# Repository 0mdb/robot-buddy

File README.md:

# Robot Buddy

A kid-safe, expressive robot platform combining real-time motor control, an animated TFT face, and optional networked AI planner.

## How It Works

Two ESP32-S3 microcontrollers handle the deterministic, safety-critical work: one drives motors with PID control and enforces safety limits, the other renders an animated face on a 320x240 TFT touch display (`esp32-face`). A Raspberry Pi 5 orchestrates everything at 50 Hz — reading sensors, running the state machine, applying layered safety policies, and streaming telemetry to a browser UI. An optional AI planner server on a separate machine (3090 Ti) generates expressive behavior plans via a local LLM.

Reflexes are local and deterministic. Planner is remote and optional.

## Hardware

| Component | Hardware | Role |
|---|---|---|
| Supervisor | Raspberry Pi 5 | 50 Hz orchestration, safety policy, HTTP/WS API |
| Face MCU | ESP32-S3 (Freenove FNK0104) | 320x240 TFT face renderer + touch/buttons telemetry |
| Reflex MCU | ESP32-S3 WROOM | Differential drive, PID, encoders, IMU, ultrasonic, safety |
| AI Server | PC with 3090 Ti (off-robot) | Planner/conversation LLM + TTS on LAN (`LLM_BACKEND=ollama|vllm`) |
| Motor Driver | TB6612FNG | Dual H-bridge for differential drive |
| Power | 2S LiPo | Split into dirty (motors) and clean 5V regulated rails |

## Repository Layout

```
robot-buddy/
├── supervisor/       # Python supervisor (Raspberry Pi 5, process-isolated workers)
│   ├── core/            # 50 Hz tick loop, state machine, safety, behavior engine
│   ├── devices/         # MCU clients (reflex, face), protocol, expressions
│   ├── io/              # Serial transport, COBS framing, CRC
│   ├── workers/         # Process-isolated workers (TTS, vision, AI)
│   ├── messages/        # NDJSON envelope, event/action types
│   ├── api/             # FastAPI HTTP/WebSocket server, param registry
│   ├── mock/            # Mock Reflex MCU for testing (PTY-based)
│   ├── tests/           # pytest test suite
│   └── pyproject.toml   # Package metadata, deps
├── server/              # AI planner server (3090 Ti, FastAPI + backend switch)
│   ├── app/             # FastAPI app, LLM/STT/TTS backends, prompts, schemas
│   ├── tests/           # pytest test suite
│   ├── Modelfile        # Legacy Ollama model config
│   └── pyproject.toml   # Package metadata, deps
├── esp32-face/       # Face MCU firmware (ESP32-S3, C/C++, ESP-IDF)
│   └── main/            # TFT face rendering + touch/buttons + USB protocol
├── esp32-reflex/        # Reflex MCU firmware (ESP32-S3, C/C++, ESP-IDF)
│   └── main/            # Differential drive, PID, IMU, safety, encoders
├── dashboard/           # React dashboard (Vite + TypeScript + Biome)
│   └── src/             # Components, hooks, stores, tabs
├── specs/               # Completed specifications (immutable reference)
├── docs/                # TODO, architecture, protocols, wiring, power, research
├── deploy/              # Deployment (systemd service, install/update scripts)
├── tools/               # Dev utilities (face sim V3, parity check)
└── training/            # Wake word model training
```

## Architecture

```
┌──────────────────────────────────────────────────────┐
│ On Robot                                             │
│                                                      │
│  ┌────────────────────────────────────────────────┐  │
│  │ Raspberry Pi 5 — Supervisor                    │  │
│  │                                                │  │
│  │  50 Hz tick loop:                              │  │
│  │    read telemetry → state machine → safety     │  │
│  │    policies → send commands → broadcast        │  │
│  │                                                │  │
│  │  HTTP API (:8080)  WebSocket (:8080/ws)        │  │
│  │  Vision process (separate OS process, 10-20Hz) │  │
│  └──────┬──────────────────────┬──────────────────┘  │
│         │ USB serial (COBS)    │ USB serial (COBS)   │
│  ┌──────▼──────┐        ┌─────▼───────┐             │
│  │ Reflex MCU  │        │  Face MCU   │             │
│  │ ESP32-S3    │        │  ESP32-S3   │             │
│  │             │        │             │             │
│  │ Motors, PID │        │ 320x240 TFT │             │
│  │ Encoders    │        │ Face +      │             │
│  │ IMU, Range  │        │ Touch UI    │             │
│  │ Safety      │        │             │             │
│  └─────────────┘        └─────────────┘             │
└──────────────────────────────────────────────────────┘
         │
         │ HTTP (LAN, optional)
         │
┌────────▼───────────────────────────┐
│ AI Server (3090 Ti PC)             │
│                                    │
│ FastAPI planner server             │
│ LLM backend: ollama | vllm         │
│ TTS: Orpheus (vLLM) + espeak shed  │
│ POST /plan / WS /converse /tts     │
└────────────────────────────────────┘
```

### State Machine

`BOOT` → `IDLE` → `TELEOP` / `WANDER` → `ERROR`

- **BOOT → IDLE**: automatic when Reflex MCU connects with no faults
- **IDLE → TELEOP/WANDER**: via `set_mode` command
- **Any → ERROR**: on disconnect, ESTOP, TILT, or BROWNOUT
- **ERROR → IDLE**: via `clear_error()` when Reflex is healthy

### Safety Policies (Defense in Depth)

1. Mode gate — no motion outside TELEOP/WANDER
2. Fault gate — any fault → zero twist
3. Reflex disconnect → zero twist
4. Ultrasonic range scaling (hard stop at 250 mm, 50% at 500 mm)
5. Stale range fallback (50% cap)
6. Vision confidence scaling
7. Stale vision timeout (500 ms)

Safety-critical enforcement also runs on the Reflex MCU itself (acceleration limits, command TTL, hard stop). The supervisor applies additional caps above this.

### Serial Protocol

Binary packets over USB serial with COBS framing:

```
[type:u8][seq:u8][payload:N][crc16:u16-LE]
```

For `esp32-face`, this protocol carries face state/gesture/system/talking commands and touch/button/status telemetry only. Audio transport is supervisor-side USB audio.

Auto-reconnect with exponential backoff (0.5s–5s). See `docs/protocols.md` for packet definitions.

## Tech Stack

| Component | Stack |
|---|---|
| Supervisor | Python 3.11+, asyncio, FastAPI, uvicorn, pyserial, OpenCV |
| AI Server | Python 3.11+, FastAPI, httpx, Pydantic, Ollama (compat) + vLLM (migration target) |
| ESP32 Firmware | C/C++, ESP-IDF (FreeRTOS), CMake |
| Build (Python) | Hatchling via pyproject.toml, uv for dependency management |
| Build (ESP32) | `idf.py build` (CMake), `source ~/esp/esp-idf/export.sh` |
| Dashboard | React 19, Vite, TypeScript, Zustand, TanStack Query |
| Tests | pytest, pytest-asyncio, Vitest |
| Linting | ruff (Python), clang-format + cppcheck (C++), Biome (TypeScript) |

## Getting Started

### Supervisor (Raspberry Pi 5)

```bash
cd supervisor
uv sync --group dev

# Run with mock hardware (no physical robot needed)
just run-mock

# Run with real hardware
just run

# Other options
uv run python -m supervisor --no-vision         # Disable vision worker
uv run python -m supervisor --http-port 8080    # Custom HTTP port
uv run python -m supervisor --planner-api http://10.0.0.20:8100 --robot-id robot-1
```

### AI Planner Server (3090 Ti PC)

```bash
# Install and run the server
cd server
uv sync --extra dev --extra llm --extra stt --extra tts

# Recommended testing profile (vLLM planner + CPU STT + espeak)
LLM_BACKEND=vllm STT_DEVICE=cpu TTS_BACKEND=espeak \
uv run --extra llm --extra stt --extra tts python -m app.main
```

The server starts on port 8100. See `server/README.md` for full API docs and configuration.

### ESP32 Firmware

Requires ESP-IDF toolchain.

```bash
cd esp32-face   # or esp32-reflex
idf.py build
idf.py flash
idf.py monitor
```

### Dashboard

```bash
just run-dashboard         # dev server with hot reload
just build-dashboard       # production build → supervisor/static/
```

## Development

All commands are available via `just` (see `justfile`):

```bash
just test-all              # run all tests (supervisor, server, dashboard)
just lint                  # check Python + C++ + dashboard
just lint-fix              # auto-fix formatting
just preflight             # full pre-commit check (lint + tests + parity)
just sim                   # run face simulator V3
just check-parity          # verify sim↔MCU constant alignment
```

### Mock Mode

The supervisor includes a PTY-based mock Reflex MCU (`supervisor/mock/mock_reflex.py`) that simulates serial communication, telemetry, and fault injection. Use `just run-mock` to run the full supervisor stack without any hardware.

### Dashboard

When the supervisor is running, open `http://<robot_ip>:8080` in a browser for:
- Live telemetry display with diagnostic tree
- Mode control (IDLE, TELEOP, WANDER)
- E-STOP button
- Face control (moods, gestures, talking, conversation state)
- Parameter tuning sliders (PID gains, speed limits, safety thresholds)
- Monitor tab (device health, comms, power, sensors, faults, workers)
- MJPEG video stream (if vision enabled)

### Configuration

**Supervisor** — YAML config file (schema in `supervisor/config.py`):
- Sections: serial, control, safety, network, logging, vision
- Default serial paths: `/dev/robot_reflex`, `/dev/robot_face` (via udev symlinks)

**AI Server** — environment variables:
- `LLM_BACKEND`, `VLLM_MODEL_NAME`, `LLM_MAX_INFLIGHT`, `PERFORMANCE_MODE`
- legacy compatibility: `OLLAMA_URL`, `MODEL_NAME`, `PLAN_TIMEOUT_S`, `TEMPERATURE`, `NUM_CTX`
- See `server/README.md` for the full table

**ESP32** — `sdkconfig.defaults` + `config.h` constants

## Supervisor API

| Endpoint | Method | Description |
|---|---|---|
| `/status` | GET | Current robot state (JSON) |
| `/params` | GET | Full parameter registry |
| `/params` | POST | Transactional parameter updates |
| `/actions` | POST | RPC: `set_mode`, `e_stop`, `clear_e_stop` |
| `/video` | GET | MJPEG stream (if vision enabled) |
| `/debug/devices` | GET | Device connection state |
| `/debug/planner` | GET | Planner state |
| `/debug/mcu_benchmark` | GET | MCU benchmark run status |
| `/ws` | WS | Telemetry stream (20 Hz, JSON) |
| `/ws/logs` | WS | Live log stream |

## AI Server API

| Endpoint | Method | Description |
|---|---|---|
| `/health` | GET | Server + selected LLM backend status |
| `/plan` | POST | Accept world state + `robot_id/seq/monotonic_ts_ms`, return plan + `plan_id` echo metadata |
| `/converse` | WS | Conversation stream (single active session per `robot_id`) |
| `/tts` | POST | Direct TTS with optional metadata (`robot_id`, `seq`, `monotonic_ts_ms`) |

Plan actions: `say(text)`, `emote(name, intensity)`, `gesture(name, params)`, `skill(name)` — planner proposes intent and supervisor executes deterministic skills.

## Supervisor Fallback Policy

| Failure condition | Immediate supervisor action | Motion policy | Face policy | Speech policy |
|---|---|---|---|---|
| `/plan` unreachable / non-200 | Mark planner disconnected; skip remote plan apply | Local deterministic only (`patrol_drift`/`avoid_obstacle`/safe stop) | `confused` gesture with cooldown | Cancel queued planner speech |
| `/converse` TTS fails mid-turn | Stop playback and clear talking flag | No change to motion authority | Show `thinking` briefly then restore previous mood | Attempt fallback backend once; if unavailable, skip speech |

## Project Status

### Working
- [x] Supervisor: 50 Hz control loop, state machine, safety policies, conversation state, mood choreography
- [x] Supervisor: serial transport with COBS framing, CRC, auto-reconnect, protocol v2 (timestamps + seq)
- [x] Supervisor: FastAPI HTTP/WebSocket API with telemetry streaming
- [x] Supervisor: process-isolated workers (TTS, vision, AI, ear)
- [x] Supervisor: mock Reflex MCU for hardware-free development
- [x] AI Server: FastAPI + vLLM planner (Qwen), conversation, TTS (Orpheus + espeak)
- [x] ESP32 Face: TFT face rendering, 13 moods, 13 gestures, conversation border, touch/button telemetry
- [x] ESP32 Reflex: motor control, PID, encoders, IMU, safety enforcement
- [x] Dashboard: React 19, live telemetry, face control, monitor tab, mode control
- [x] Voice pipeline: wake word ("hey buddy") + VAD → STT → LLM → TTS → face animation
- [x] WANDER mode driven by deterministic skills + planner intent
- [x] Deterministic telemetry: timestamps, sequence numbers, clock sync, raw packet logging

### In Progress
- [ ] Reflex MCU hardware commissioning (breadboard bring-up)
- [ ] Personality engine implementation (spec complete, implementation pending)

### Future
- [ ] Conversation memory / interaction history
- [ ] Wake word model improvements (recall 42% → 80%+)
- [ ] Additional modes: LINE_FOLLOW, BALL, CRANE, CHARGING
- [ ] Home Assistant integration
- [ ] Voice ID / speaker identification

See [docs/TODO.md](docs/TODO.md) for the detailed backlog and [specs/](specs/) for design specifications.

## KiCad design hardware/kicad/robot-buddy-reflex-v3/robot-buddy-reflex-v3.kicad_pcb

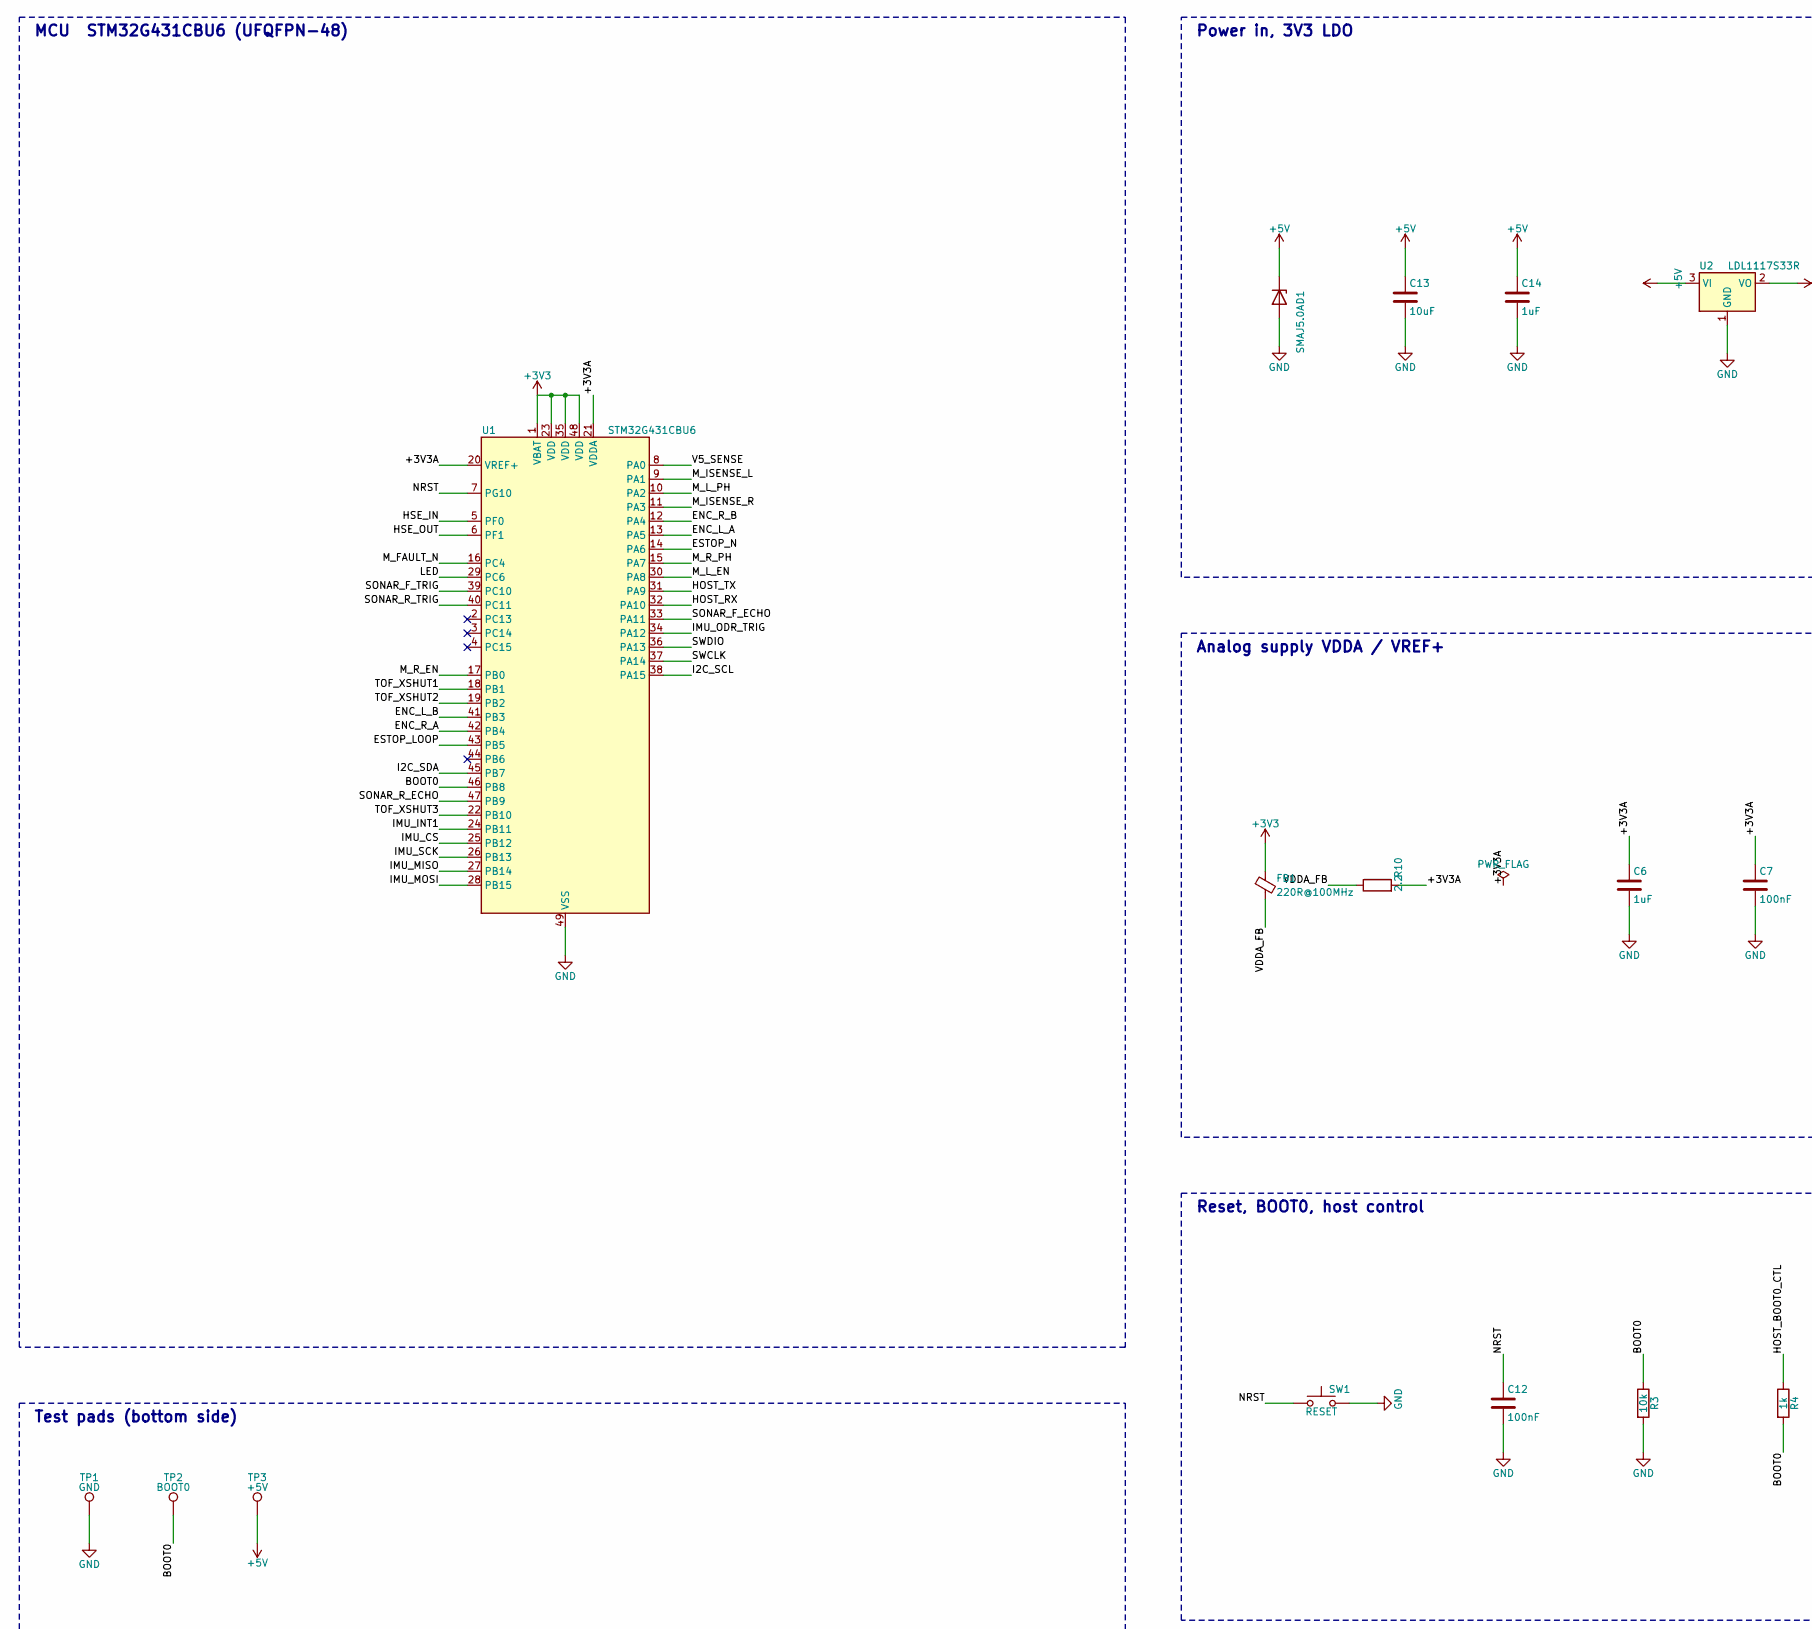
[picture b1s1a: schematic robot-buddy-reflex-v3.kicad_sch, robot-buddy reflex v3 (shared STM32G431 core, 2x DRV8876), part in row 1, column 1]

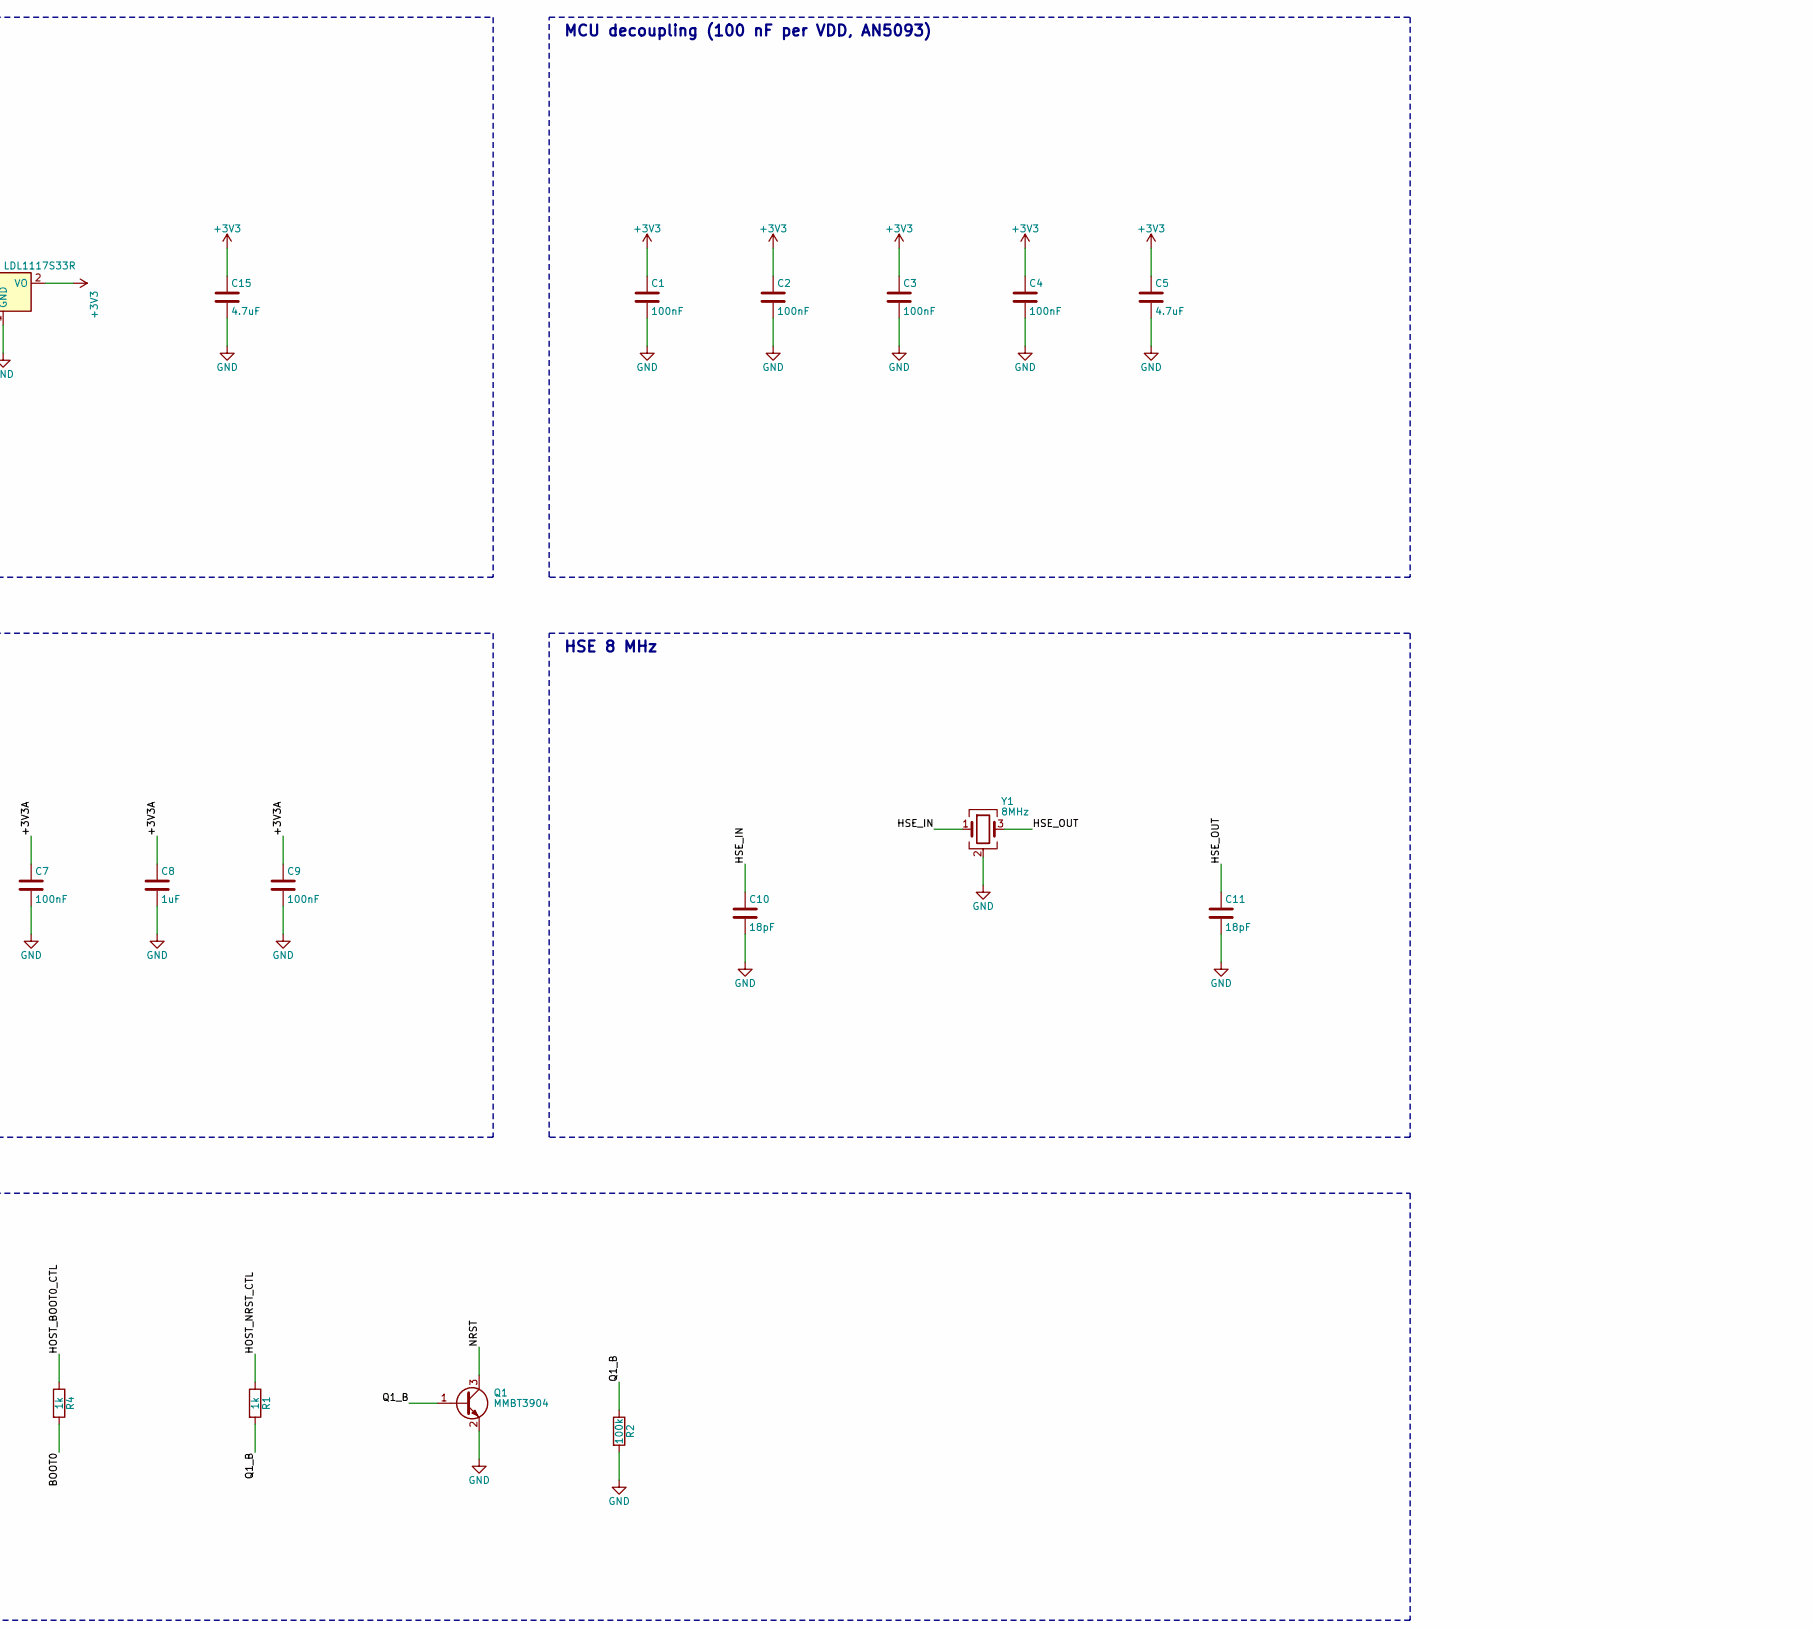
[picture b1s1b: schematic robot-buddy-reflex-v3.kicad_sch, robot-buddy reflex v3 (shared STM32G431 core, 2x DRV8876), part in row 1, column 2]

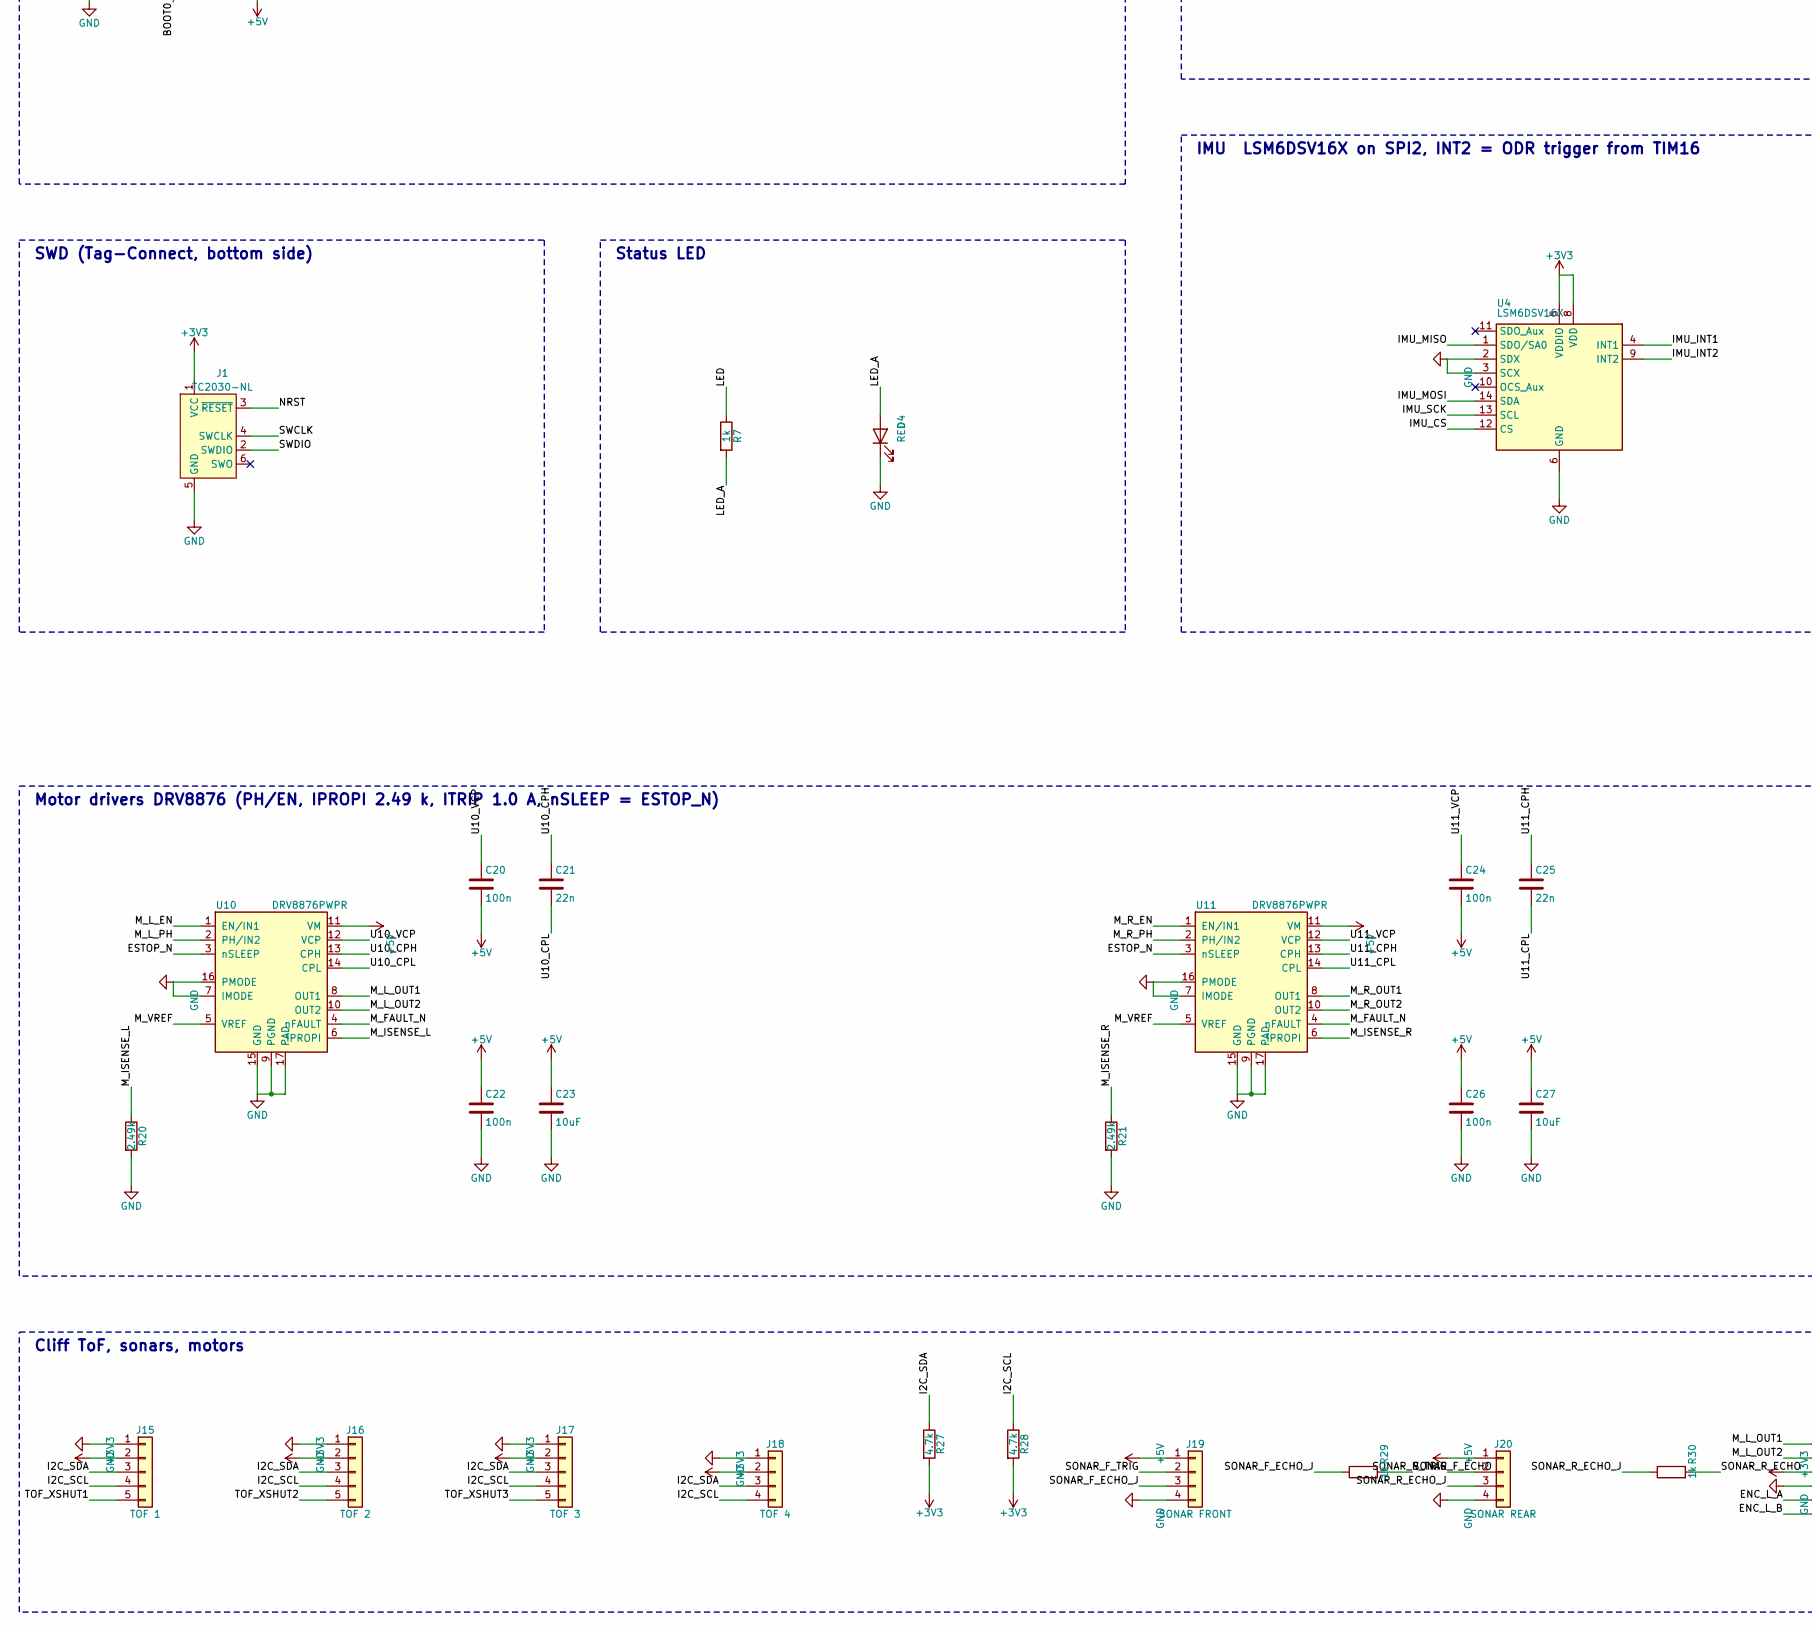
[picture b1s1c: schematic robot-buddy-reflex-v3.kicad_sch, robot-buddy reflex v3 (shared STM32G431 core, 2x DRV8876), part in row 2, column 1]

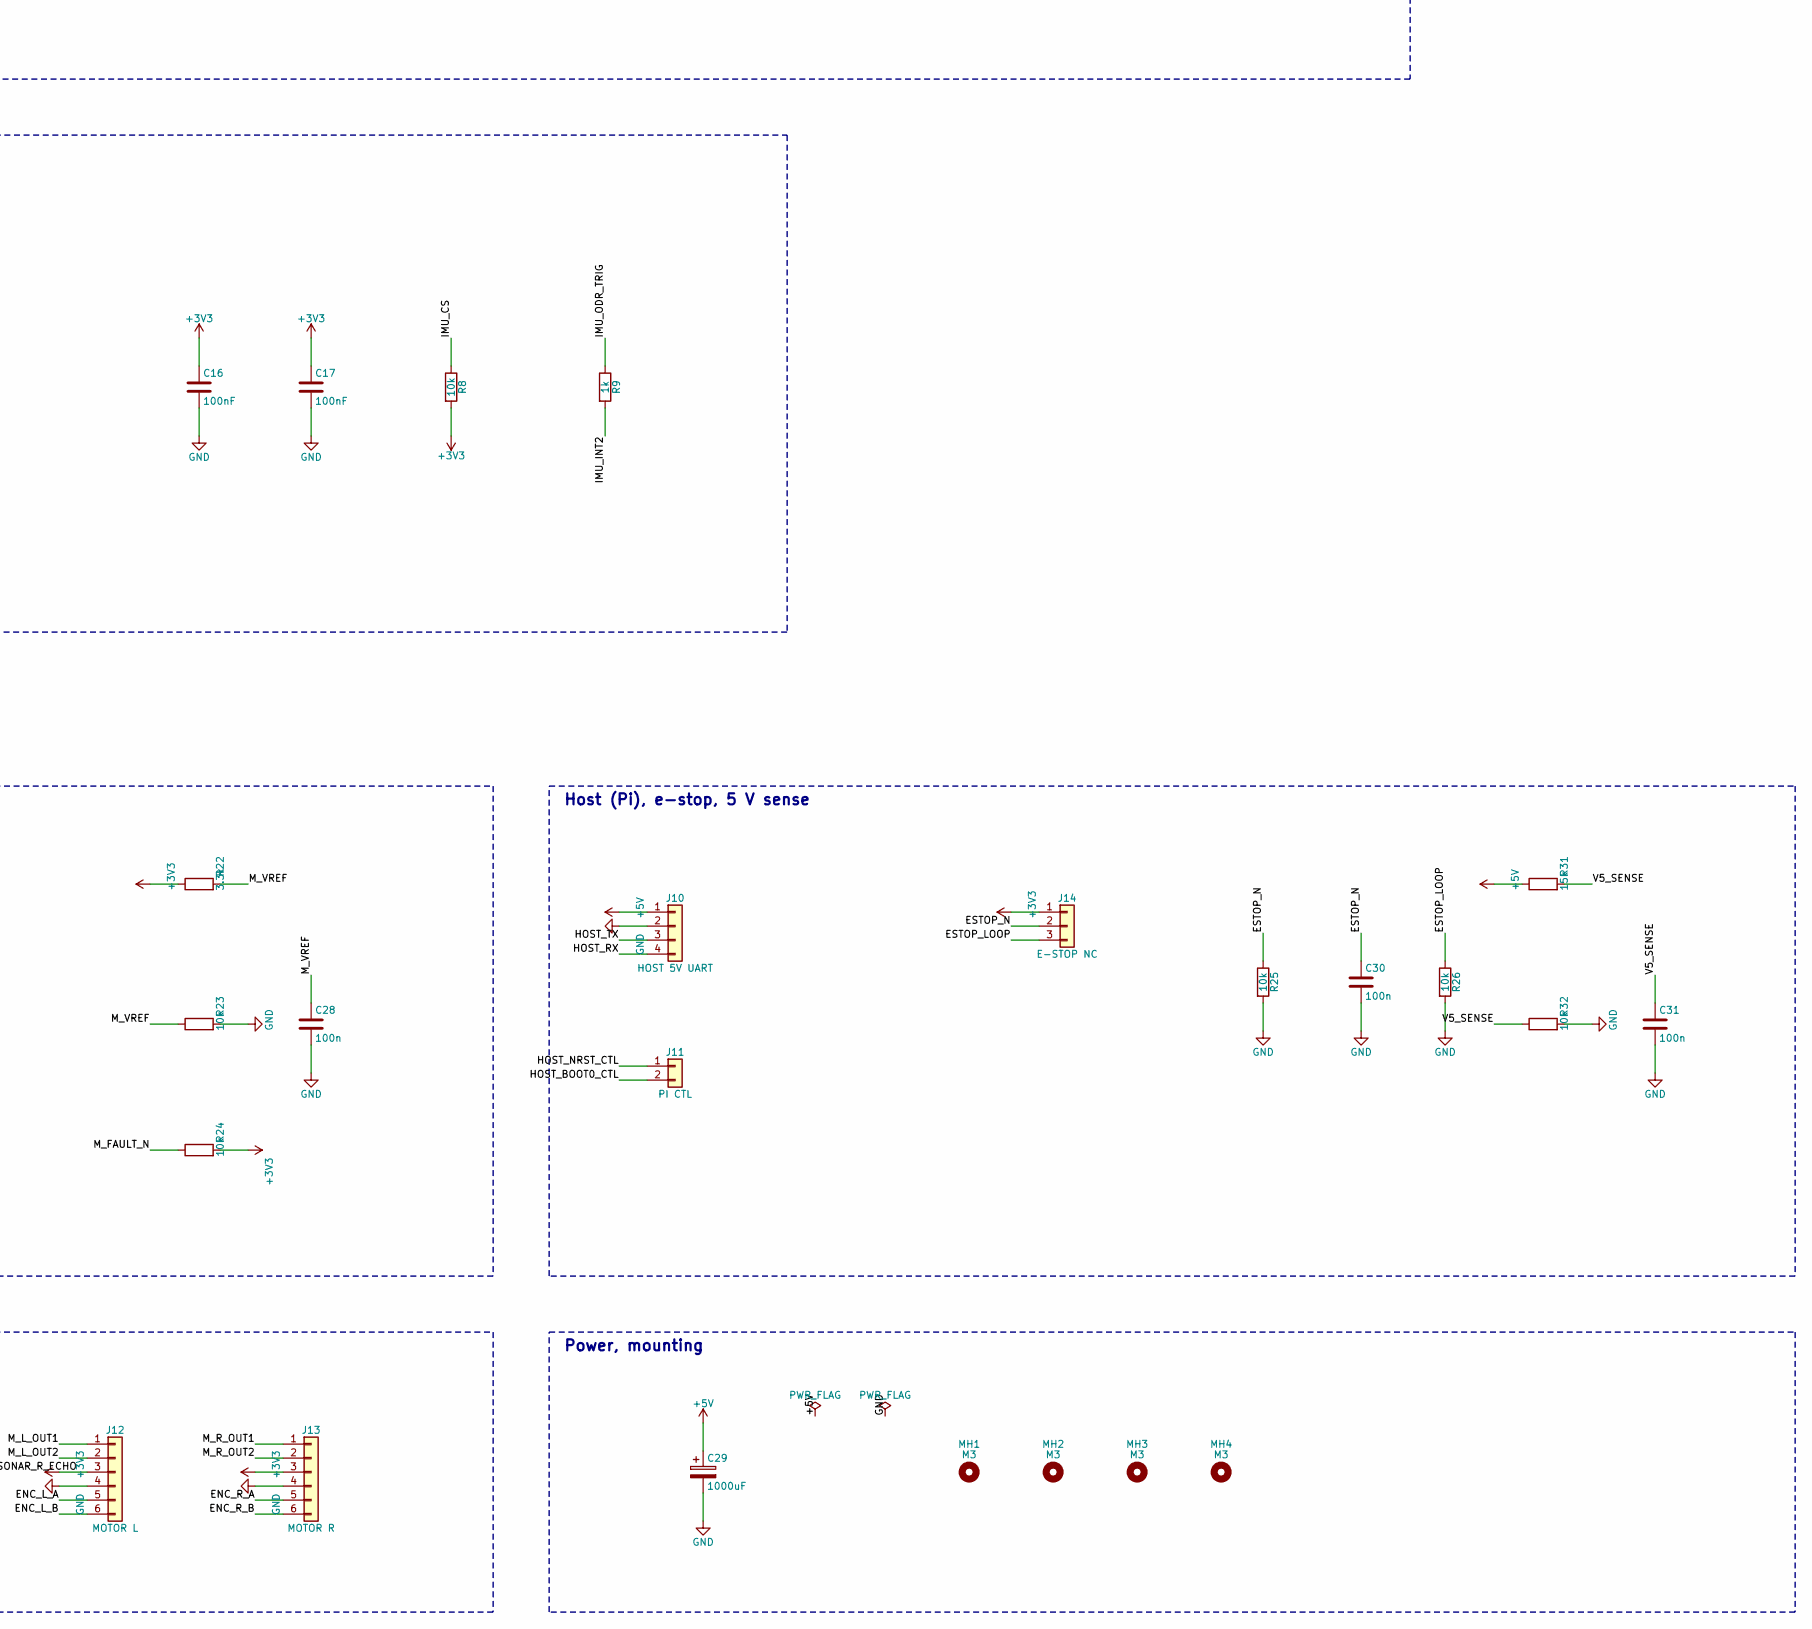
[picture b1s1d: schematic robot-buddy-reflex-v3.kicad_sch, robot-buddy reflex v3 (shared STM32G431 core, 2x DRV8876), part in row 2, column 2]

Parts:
C1, C2, C3, C4, C7, C9, C12, C16, C17: 100nF; C_0402_1005Metric; LCSC C1525
C5, C15: 4.7uF; C_0603_1608Metric; LCSC C19666
C6, C8, C14: 1uF; C_0402_1005Metric; LCSC C52923
C10, C11: 18pF; C_0402_1005Metric; LCSC C1549
C13, C23, C27: 10uF; C_0805_2012Metric; LCSC C15850
C20, C22, C24, C26, C28, C30, C31: 100n; C_0402_1005Metric; LCSC C1525
C21, C25: 22n; C_0402_1005Metric; LCSC C337699
C29: 1000uF; CP_Radial_D10.0mm_P5.00mm
D1: SMAJ5.0A; D_SMA; LCSC C5189780
D4: RED; LED_0603_1608Metric; LCSC C2286
FB1: 220R@100MHz; L_0603_1608Metric; LCSC C80165
J1: TC2030-NL; Tag-Connect_TC2030-IDC-NL_2x03_P1.27mm_Vertical
J10: HOST 5V UART; JST_VH_B4P-VH_1x04_P3.96mm_Vertical
J11: PI CTL; JST_XH_B2B-XH-A_1x02_P2.50mm_Vertical; LCSC C265283
J12: MOTOR L; JST_XH_B6B-XH-A_1x06_P2.50mm_Vertical; LCSC C265366
J13: MOTOR R; JST_XH_B6B-XH-A_1x06_P2.50mm_Vertical; LCSC C265366
J14: E-STOP NC; JST_XH_B3B-XH-A_1x03_P2.50mm_Vertical; LCSC C144394
J15: TOF 1; JST_SH_BM05B-SRSS-TB_1x05-1MP_P1.00mm_Vertical; LCSC C54582900
J16: TOF 2; JST_SH_BM05B-SRSS-TB_1x05-1MP_P1.00mm_Vertical; LCSC C54582900
J17: TOF 3; JST_SH_BM05B-SRSS-TB_1x05-1MP_P1.00mm_Vertical; LCSC C54582900
J18: TOF 4; JST_SH_BM04B-SRSS-TB_1x04-1MP_P1.00mm_Vertical; LCSC C160390
J19: SONAR FRONT; PinHeader_1x04_P2.54mm_Vertical
J20: SONAR REAR; PinHeader_1x04_P2.54mm_Vertical
MH1, MH2, MH3, MH4: M3; MountingHole_3.2mm_M3
Q1: MMBT3904; SOT-23; LCSC C20526
R1, R4, R7, R9, R29, R30: 1k; R_0402_1005Metric; LCSC C11702
R2: 100k; R_0402_1005Metric; LCSC C25741
R3, R8, R23, R24, R25, R26, R32: 10k; R_0402_1005Metric; LCSC C25744
R10: 2.2; R_0402_1005Metric; LCSC C25101
R20, R21: 2.49k; R_0402_1005Metric; LCSC C25884
R22: 3.3k; R_0402_1005Metric; LCSC C25890
R27, R28: 4.7k; R_0402_1005Metric; LCSC C25900
R31: 15k; R_0402_1005Metric; LCSC C25756
SW1: RESET; SW_Push_1P1T_XKB_TS-1187A; LCSC C318884
TP1: GND; TestPoint_Pad_D1.0mm
TP2: BOOT0; TestPoint_Pad_D1.0mm
TP3: +5V; TestPoint_Pad_D1.0mm
U1: STM32G431CBU6; QFN-48-1EP_7x7mm_P0.5mm_EP5.6x5.6mm; LCSC C529356
U2: LDL1117S33R; SOT-223-3_TabPin2; LCSC C435835
U4: LSM6DSV16X; LGA-14_3x2.5mm_P0.5mm_LayoutBorder3x4y; LCSC C5267406
U10, U11: DRV8876PWPR; HTSSOP-16-1EP_4.4x5mm_P0.65mm_EP3.4x5mm_Mask3x3mm_ThermalVi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; LCSC C575551
Y1: 8MHz; Crystal_SMD_3225-4Pin_3.2x2.5mm; LCSC C2842191

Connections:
+3V3: C1.1, C2.1, C3.1, C4.1, C5.1, C15.1, C16.1, C17.1, FB1.1, J1.1 (VCC), J12.3, J13.3, J14.1, J15.2, J16.2, J17.2, J18.2, R8.2, R22.1, R24.2, R27.2, R28.2, U1.1 (VBAT), U1.23 (VDD), U1.35 (VDD), U1.48 (VDD), U2.2 (VO), U4.5 (VDDIO), U4.8 (VDD)
+5V: C13.1, C14.1, C20.2, C22.1, C23.1, C24.2, C26.1, C27.1, C29.1, D1.1 (K), J10.1, J19.1, J20.1, R31.1, TP3.1, U2.3 (VI), U10.11 (VM), U11.11 (VM)
/+3V3A: C6.1, C7.1, C8.1, C9.1, R10.2, U1.20 (VREF+), U1.21 (VDDA)
/BOOT0: R3.1, R4.2, TP2.1, U1.46 (PB8)
/ENC_L_A: J12.5, U1.13 (PA5)
/ENC_L_B: J12.6, U1.41 (PB3)
/ENC_R_A: J13.5, U1.42 (PB4)
/ENC_R_B: J13.6, U1.12 (PA4)
/ESTOP_LOOP: J14.3, R26.1, U1.43 (PB5)
/ESTOP_N: C30.1, J14.2, R25.1, U1.14 (PA6), U10.3 (nSLEEP), U11.3 (nSLEEP)
/HOST_BOOT0_CTL: J11.2, R4.1
/HOST_NRST_CTL: J11.1, R1.1
/HOST_RX: J10.4, U1.32 (PA10)
/HOST_TX: J10.3, U1.31 (PA9)
/HSE_IN: C10.1, U1.5 (PF0), Y1.1
/HSE_OUT: C11.1, U1.6 (PF1), Y1.3
/I2C_SCL: J15.4, J16.4, J17.4, J18.4, R28.1, U1.38 (PA15)
/I2C_SDA: J15.3, J16.3, J17.3, J18.3, R27.1, U1.45 (PB7)
/IMU_CS: R8.1, U1.25 (PB12), U4.12 (CS)
/IMU_INT1: U1.24 (PB11), U4.4 (INT1)
/IMU_INT2: R9.2, U4.9 (INT2)
/IMU_MISO: U1.27 (PB14), U4.1 (SDO/SA0)
/IMU_MOSI: U1.28 (PB15), U4.14 (SDA)
/IMU_ODR_TRIG: R9.1, U1.34 (PA12)
/IMU_SCK: U1.26 (PB13), U4.13 (SCL)
/LED: R7.1, U1.29 (PC6)
/LED_A: D4.2 (A), R7.2
/M_FAULT_N: R24.1, U1.16 (PC4), U10.4 (nFAULT), U11.4 (nFAULT)
/M_ISENSE_L: R20.1, U1.9 (PA1), U10.6 (IPROPI)
/M_ISENSE_R: R21.1, U1.11 (PA3), U11.6 (IPROPI)
/M_L_EN: U1.30 (PA8), U10.1 (EN/IN1)
/M_L_OUT1: J12.1, U10.8 (OUT1)
/M_L_OUT2: J12.2, U10.10 (OUT2)
/M_L_PH: U1.10 (PA2), U10.2 (PH/IN2)
/M_R_EN: U1.17 (PB0), U11.1 (EN/IN1)
/M_R_OUT1: J13.1, U11.8 (OUT1)
/M_R_OUT2: J13.2, U11.10 (OUT2)
/M_R_PH: U1.15 (PA7), U11.2 (PH/IN2)
/M_VREF: C28.1, R22.2, R23.1, U10.5 (VREF), U11.5 (VREF)
/NRST: C12.1, J1.3 (~RESET), Q1.3 (C), SW1.1, U1.7 (PG10)
/Q1_B: Q1.1 (B), R1.2, R2.1
/SONAR_F_ECHO: R29.2, U1.33 (PA11)
/SONAR_F_ECHO_J: J19.3, R29.1
/SONAR_F_TRIG: J19.2, U1.39 (PC10)
/SONAR_R_ECHO: R30.2, U1.47 (PB9)
/SONAR_R_ECHO_J: J20.3, R30.1
/SONAR_R_TRIG: J20.2, U1.40 (PC11)
/SWCLK: J1.4 (SWCLK), U1.37 (PA14)
/SWDIO: J1.2 (SWDIO), U1.36 (PA13)
/TOF_XSHUT1: J15.5, U1.18 (PB1)
/TOF_XSHUT2: J16.5, U1.19 (PB2)
/TOF_XSHUT3: J17.5, U1.22 (PB10)
/U10_CPH: C21.1, U10.13 (CPH)
/U10_CPL: C21.2, U10.14 (CPL)
/U10_VCP: C20.1, U10.12 (VCP)
/U11_CPH: C25.1, U11.13 (CPH)
/U11_CPL: C25.2, U11.14 (CPL)
/U11_VCP: C24.1, U11.12 (VCP)
/V5_SENSE: C31.1, R31.2, R32.1, U1.8 (PA0)
/VDDA_FB: FB1.2, R10.1
GND: C1.2, C2.2, C3.2, C4.2, C5.2, C6.2, C7.2, C8.2, C9.2, C10.2, C11.2, C12.2, C13.2, C14.2, C15.2, C16.2, C17.2, C22.2, C23.2, C26.2, C27.2, C28.2, C29.2, C30.2, C31.2, D1.2 (A), D4.1 (K), J1.5 (GND), J10.2, J12.4, J13.4, J15.1, J16.1, J17.1, J18.1, J19.4, J20.4, Q1.2 (E), R2.2, R3.2, R20.2, R21.2, R23.2, R25.2, R26.2, R32.2, SW1.2, TP1.1, U1.49 (VSS), U2.1 (GND), U4.2 (SDX), U4.3 (SCX), U4.6 (GND), U4.7 (GND), U10.7 (IMODE), U10.9 (PGND), U10.15 (GND), U10.16 (PMODE), U10.17 (PAD), U11.7 (IMODE), U11.9 (PGND), U11.15 (GND), U11.16 (PMODE), U11.17 (PAD), Y1.2 (G), Y1.4 (G)

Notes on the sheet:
MCU STM32G431CBU6 (UFQFPN-48)
Test pads (bottom side)
SWD (Tag-Connect, bottom side)
Status LED
Power in, 3V3 LDO
MCU decoupling (100 nF per VDD, AN5093)
Analog supply VDDA / VREF+
HSE 8 MHz
Reset, BOOT0, host control
IMU LSM6DSV16X on SPI2, INT2 = ODR trigger from TIM16
Motor drivers DRV8876 (PH/EN, IPROPI 2.49 k, ITRIP 1.0 A, nSLEEP = ESTOP_N)
Host (Pi), e-stop, 5 V sense
Cliff ToF, sonars, motors
Power, mounting

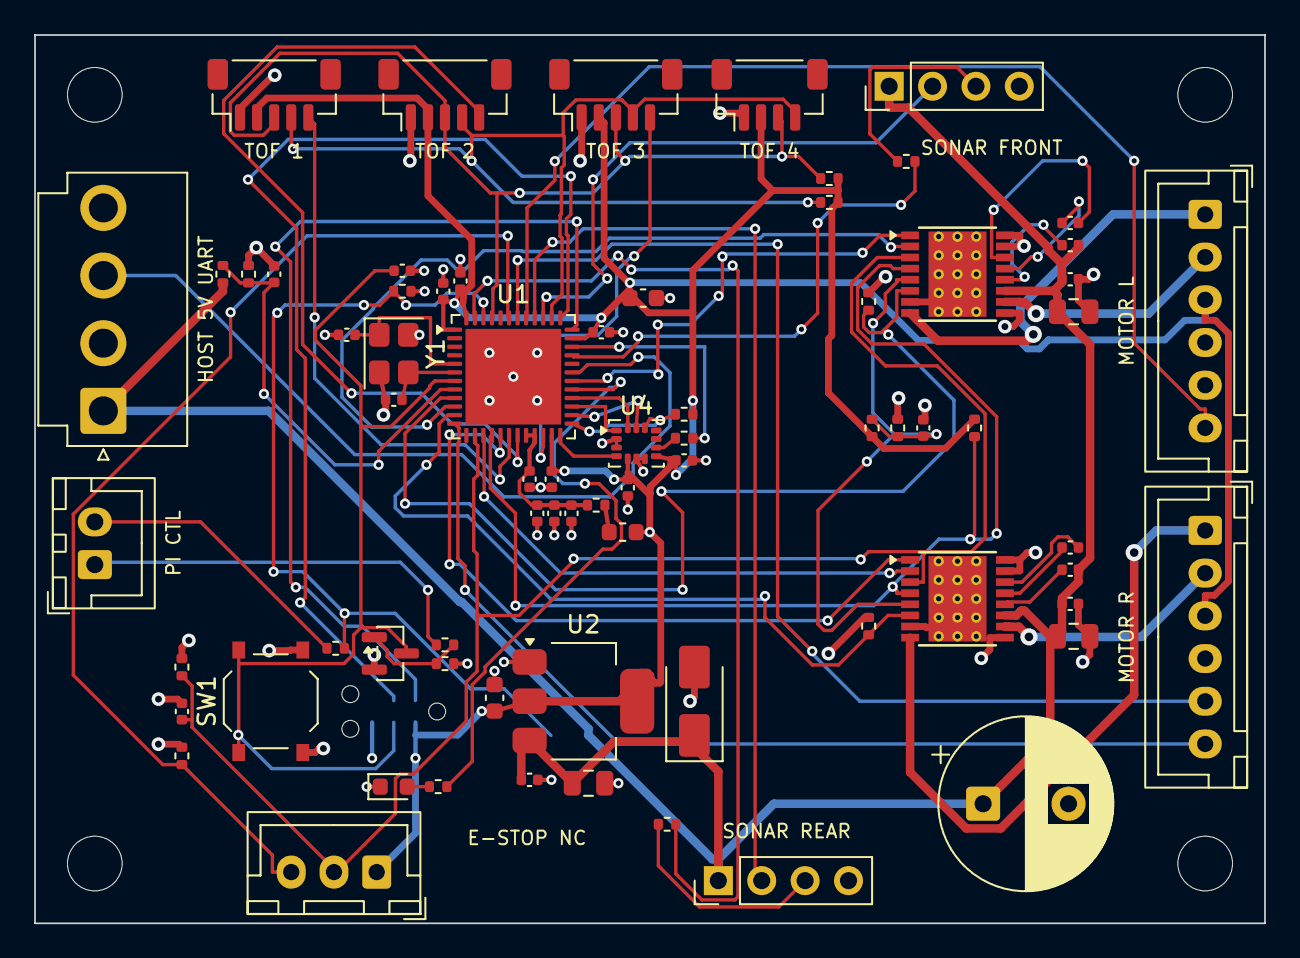
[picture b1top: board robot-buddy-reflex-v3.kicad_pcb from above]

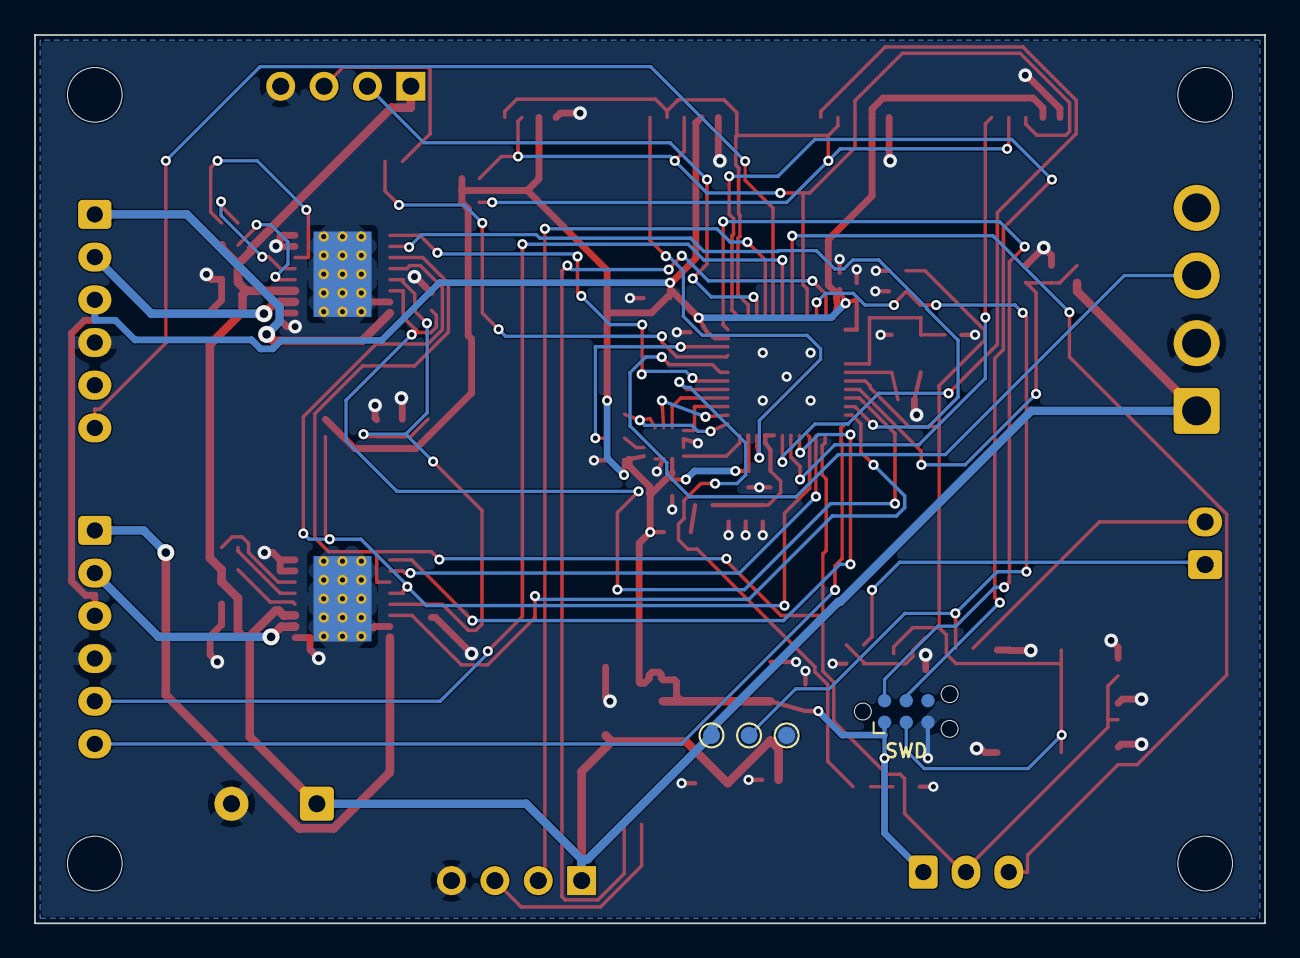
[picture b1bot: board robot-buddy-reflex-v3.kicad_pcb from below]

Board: 4 copper layers, 72.0 x 52.0 mm, 80 parts (4 on the bottom side), 61 nets.
